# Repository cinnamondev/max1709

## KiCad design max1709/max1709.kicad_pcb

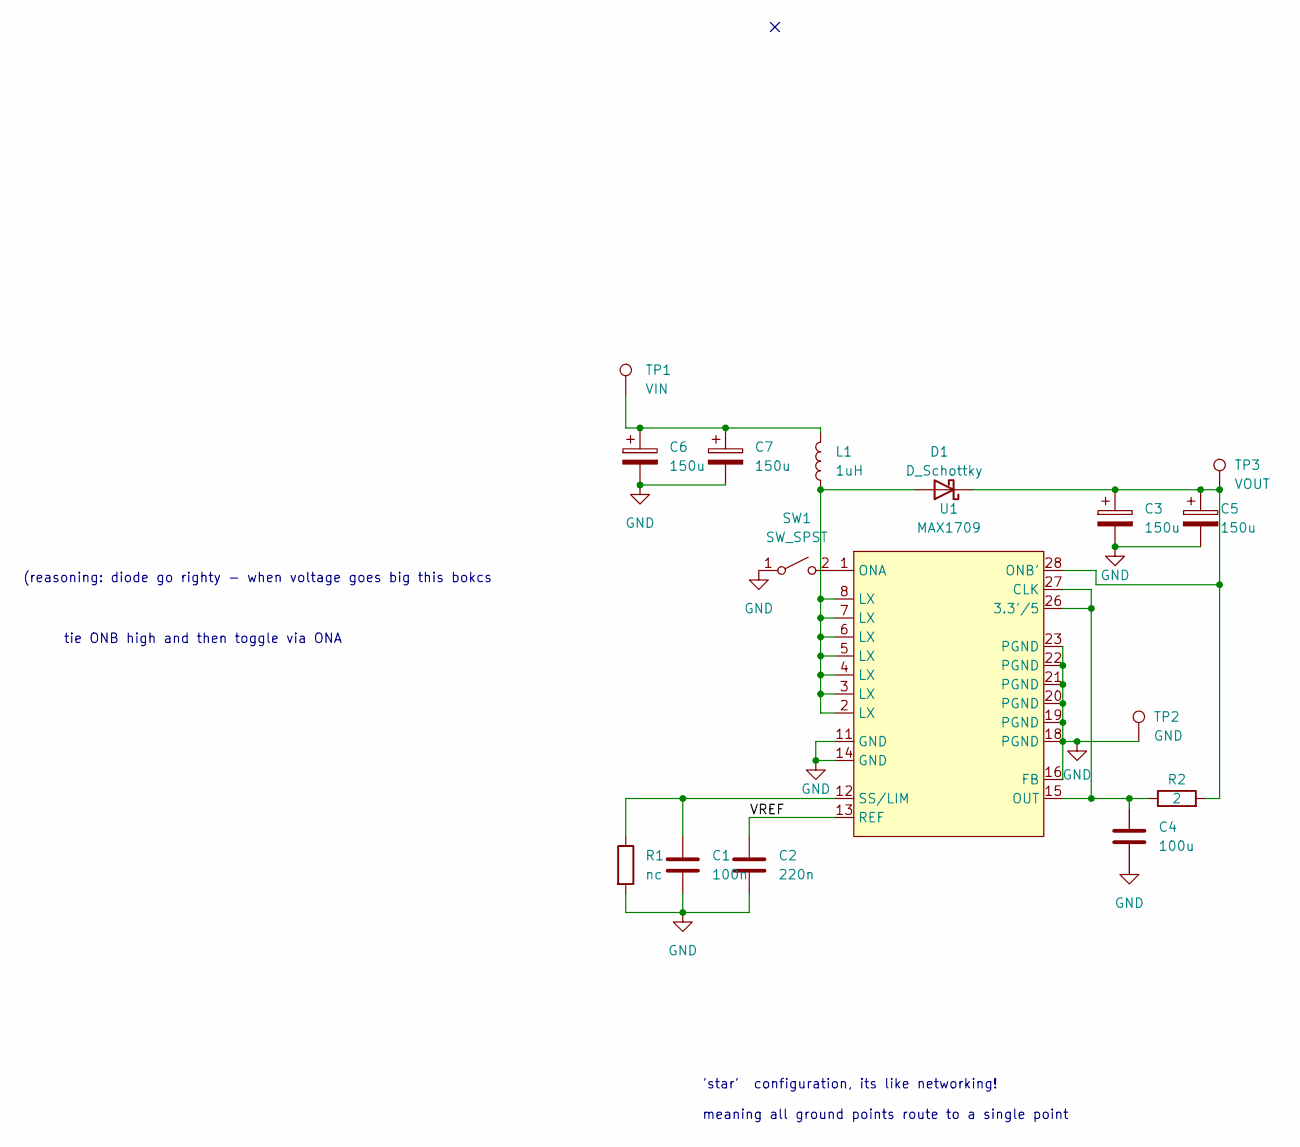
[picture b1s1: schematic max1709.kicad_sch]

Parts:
C1: 100n; C_1206_3216Metric_Pad1.33x1.80mm_HandSolder
C2: 220n; C_1206_3216Metric_Pad1.33x1.80mm_HandSolder
C3: 150u; CP_EIA-7343-15_Kemet-W_Pad2.25x2.55mm_HandSolder
C4: 100u; C_1206_3216Metric_Pad1.33x1.80mm_HandSolder
C5, C6, C7: 150u; CP_EIA-7343-31_Kemet-D_Pad2.25x2.55mm_HandSolder
D1: D_Schottky; TO-252-2
L1: 1uH; VLS5045
R1: nc; R_1206_3216Metric
R2: 2; R_1206_3216Metric_Pad1.30x1.75mm_HandSolder
SW1: SW_SPST; PinSocket_1x02_P2.54mm_Vertical
TP1: VIN; PinSocket_1x01_P2.54mm_Vertical
TP2: GND; PinSocket_1x01_P2.54mm_Vertical
TP3: VOUT; PinSocket_1x01_P2.54mm_Vertical
U1: MAX1709; TSSOP-28-1EP_4.4x9.7mm_P0.65mm_EP2.85x6.7mm

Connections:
/VREF: C2.1, U1.13 (REF)
GND: C1.2, C2.2, C3.2, C4.2, C5.2, C6.2, C7.2, R1.2, SW1.1 (A), TP2.1, U1.11 (GND), U1.14 (GND), U1.16 (FB), U1.18 (PGND), U1.19 (PGND), U1.20 (PGND), U1.21 (PGND), U1.22 (PGND), U1.23 (PGND)
unnamed: C1.1, R1.1, U1.12 (SS/LIM)
unnamed: C3.1, C5.1, D1.2 (K), R2.2, TP3.1, U1.28 (ONB')
unnamed: C4.1, R2.1, U1.15 (OUT), U1.26 (3.3'/5), U1.27 (CLK)
unnamed: C6.1, C7.1, L1.2, TP1.1
unnamed: D1.3 (A), L1.1, U1.2 (LX), U1.3 (LX), U1.4 (LX), U1.5 (LX), U1.6 (LX), U1.7 (LX), U1.8 (LX)
unnamed: SW1.2 (B), U1.1 (ONA)

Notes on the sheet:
(reasoning: diode go righty - when voltage goes big this bokcs
tie ONB high and then toggle via ONA
'star' configuration, its like networking! meaning all ground points route to a single point

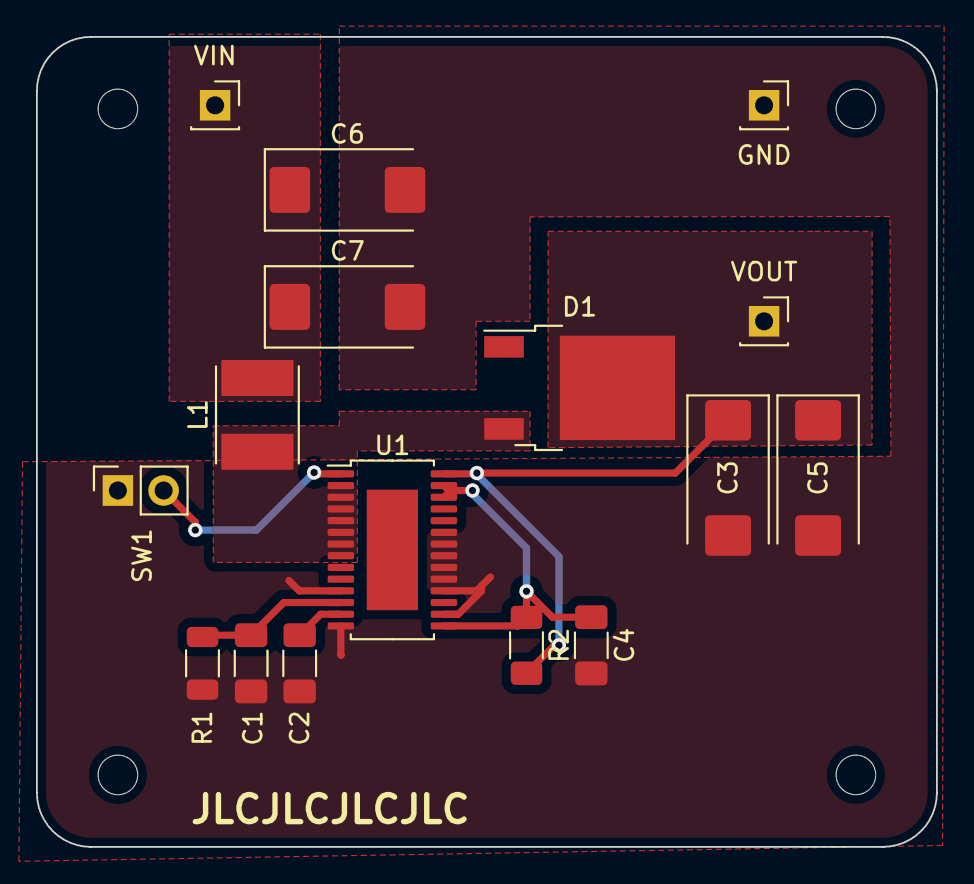
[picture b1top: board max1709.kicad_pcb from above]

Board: 2 copper layers, 50.0 x 45.0 mm, 16 parts (0 on the bottom side), 8 nets.

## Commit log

2021-11-06 reference design
2021-11-06 complete
